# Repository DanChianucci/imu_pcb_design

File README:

This Board is an Arduino Compatable IMU/MARGS solution.
Given the Correct Firmware this unit can calculate its orientation 
relative to the earth at any given time.

IMU = Inertial Measurement Unit
MARGS = Magnetic, Angular Rate, Gravity Sensor

Main Parts include:

ITG3200 	    3 axis gyroscope
ADXL345 	    3 axis accelerometer
HMC5883L 	    3 axis magnetometer
ATMEGA328P 	    Microcontroller
ATMEGA8U2 	    USB Microcontroller
PCA9306DCUR 	i2c logic level translator

!!!!!!!!NOTE!!!!!!!!!!!
	-I recently recieved the pcb and assembled my first unit.  It works perfectly.
	 However, the Resonator that I ordered (in the parts list) is too big to fit on the footprint.
	 Instead use a CSTCE16 from Murata.
	 
	 The 3x4 Interupt/ IO select header will not work with standard male headers because the holes are too small.
	 Workaround by using swiss machine pin headers, or headers with a small diameter pin.

These Schematics and Board Layout Files were created using EagleCad Which can be
found at:
    http://www.cadsoftusa.com/
	
Additionally, many footprints and symbols were taken from the Sparkfun Eagle 
Library which can be found at:
	https://github.com/sparkfun/SparkFun-Eagle-Library

This project is not affiliated with Arduino which can be read about at:
	http://www.arduino.cc/

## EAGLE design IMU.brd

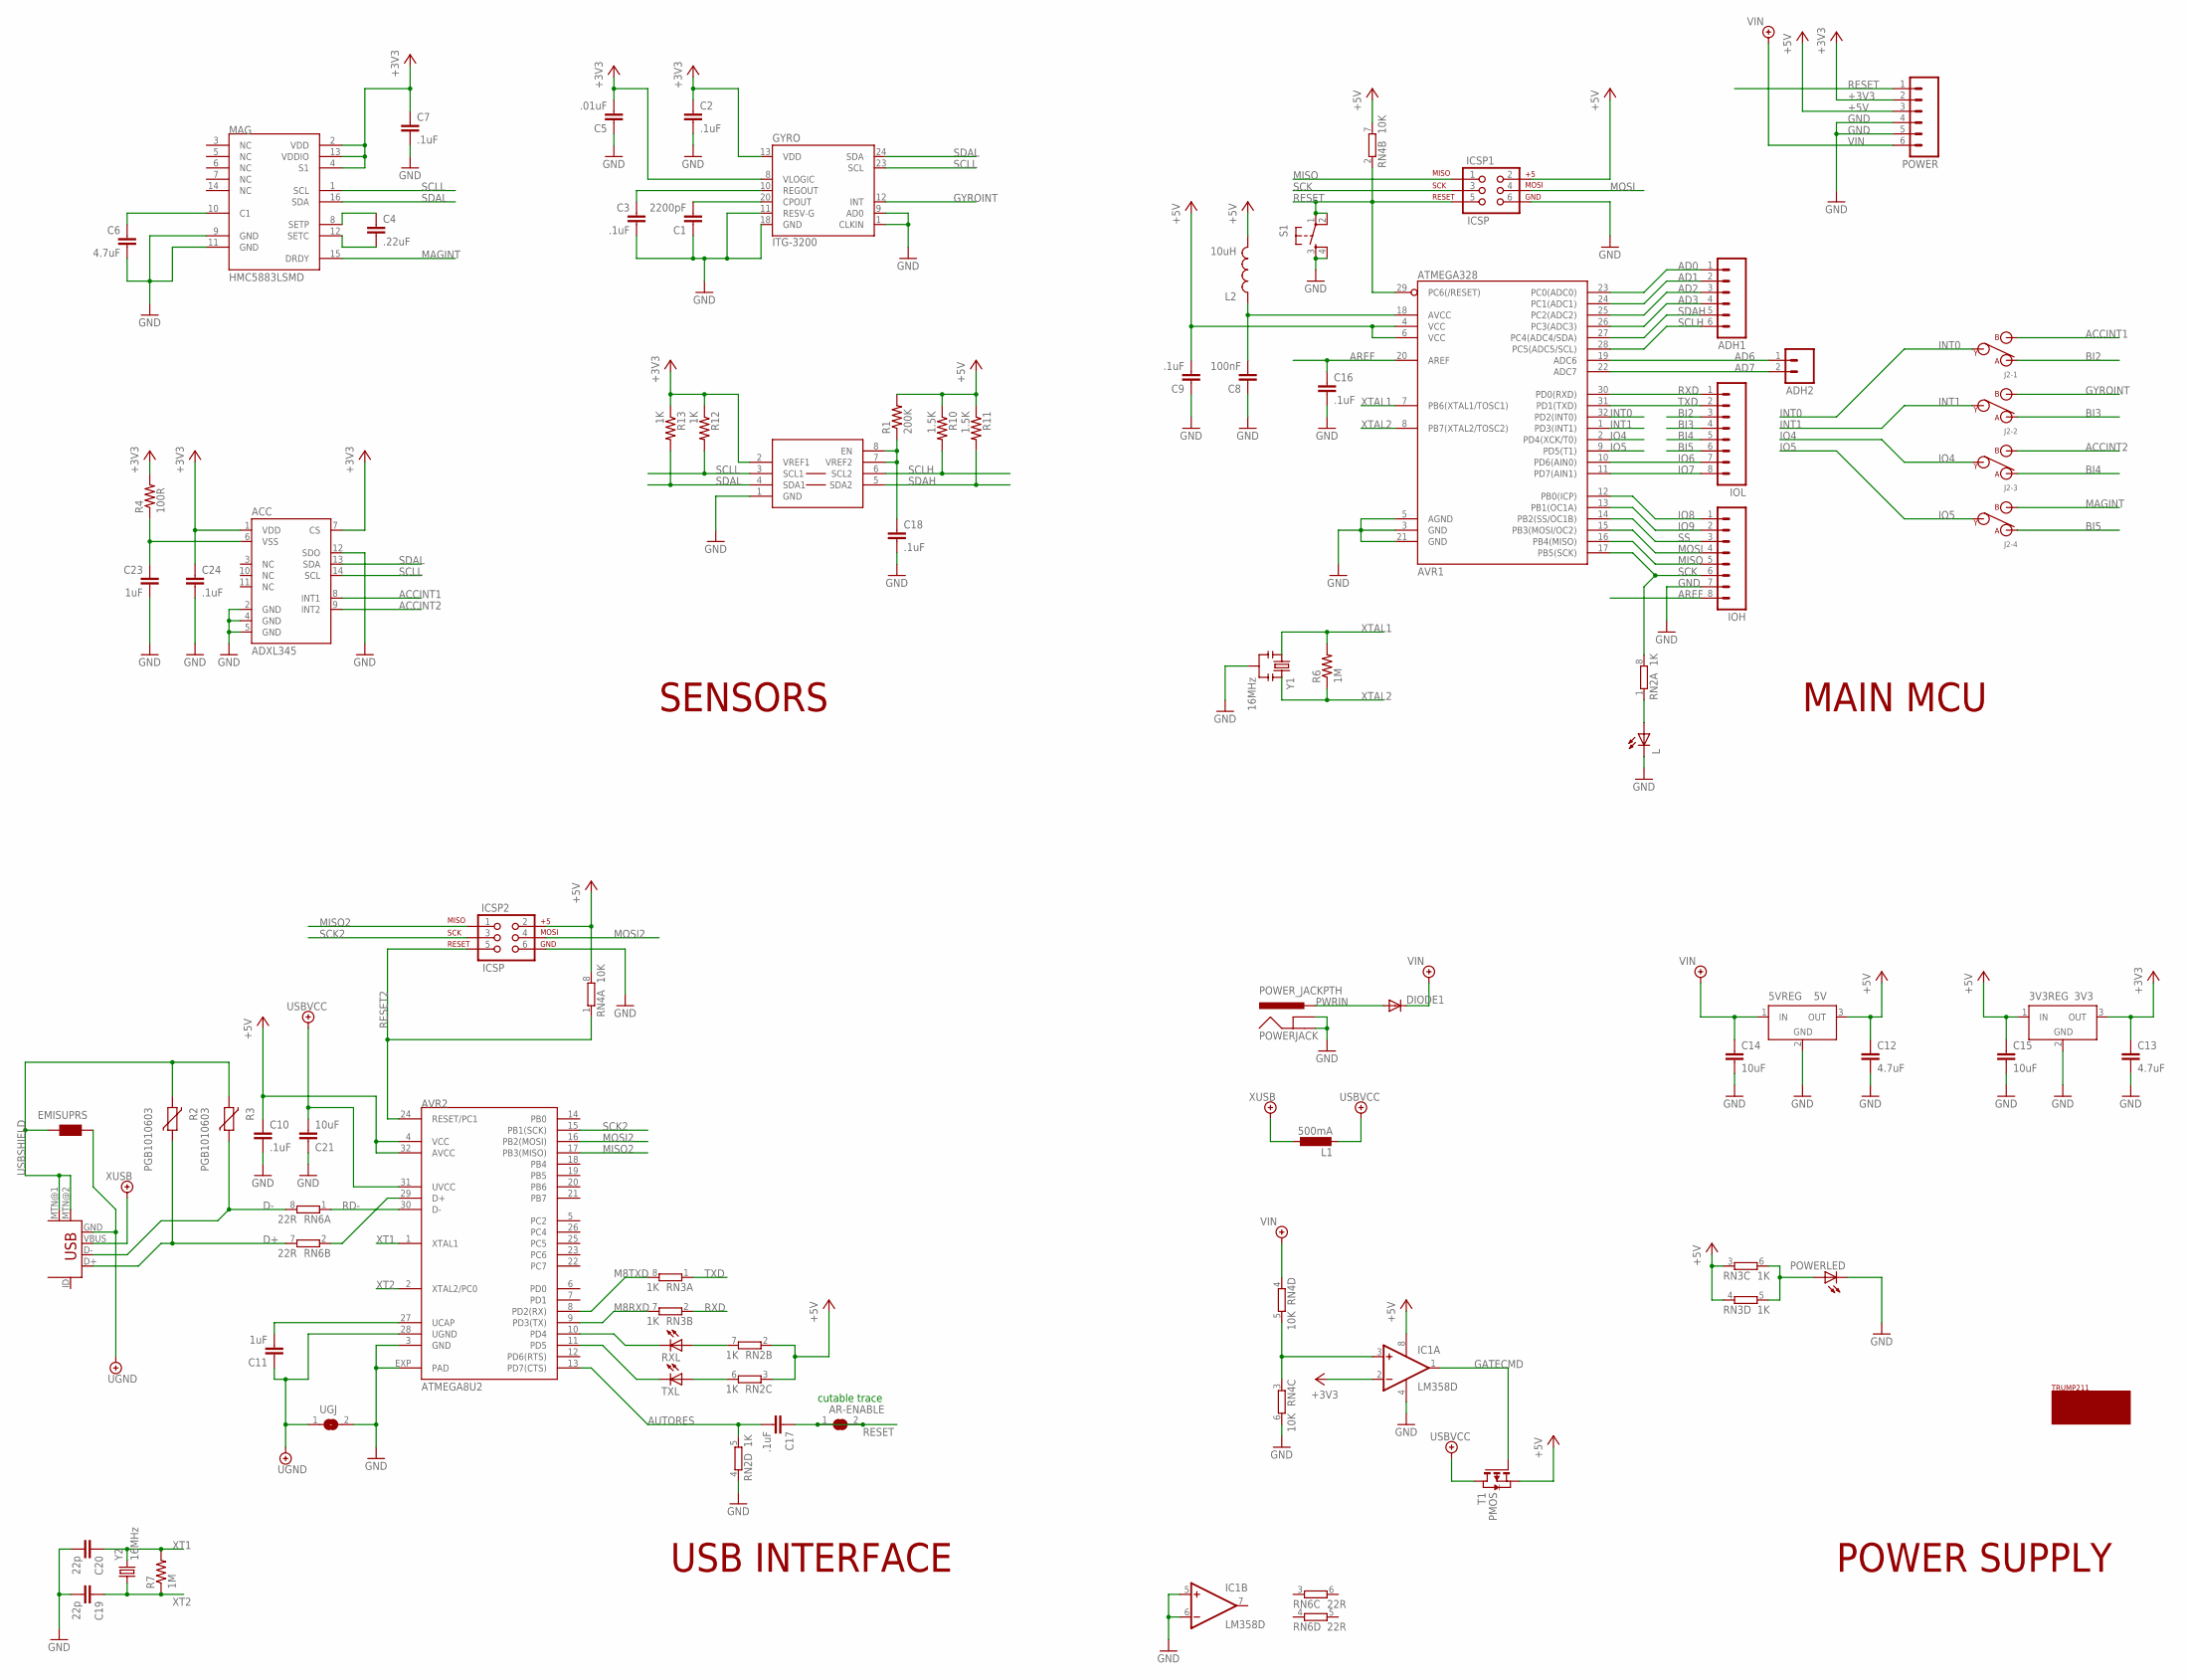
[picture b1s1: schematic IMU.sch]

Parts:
3V3REG: 3V3; SOT223
5VREG: 5V; SOT223
ACC: ADXL345; LGA14
ADH1: M06LOCK; 1X06_LOCK
ADH2: M02LOCK; 1X02_LOCK
AR-ENABLE: SJ
AVR1: ATMEGA328; TQFP32-08
AVR2: ATMEGA8U2; QFN32
C1: 2200pF; C0603
C2, C3, C7, C9, C10, C16, C17, C18, C24: .1uF; C0603
C4: .22uF; C0805
C5: .01uF; C0603
C6: 4.7uF; C0805
C8: 100nF; C0603
C11: 1uF; C0603
C12, C13: 4.7uF; C1206
C14, C15: 10uF; C1206
C19, C20: 22p; C0603
C21: 10uF; C0805
C23: 1uF; C0805
DIODE1: DIODESMA; SMA-DIODE
EMISUPRS: WE-CBF_0805; 0805
GYRO: ITG-3200; QFN-24
IC1: LM358D; SO08
ICSP1, ICSP2: ICSP; 2X3_LOCK
IOH: M08LOCK; 1X08_LOCK
IOL: M08LOCK; 1X08_LOCK
J2: 4POS_SPDT_DIP; 4X3_JUMP
L: LEDCHIP-LED0805; CHIP-LED0805
L1: 500mA; L1812
L2: 10uH; 0805
MAG: HMC5883LSMD; 16LPCC
MINIUSB: USBMINI
POWER: M06LOCK; 1X06_LOCK
POWERJACK: POWER_JACKPTH; POWER_JACK_PTH
POWERLED: LEDCHIP-LED0805; CHIP-LED0805
R1: 200K; R0603
R2, R3: PGB1010603; CT/CN0603
R4: 100R; R0603
R6, R7: 1M; R0603
R10, R11: 1.5K; R0603
R12, R13: 1K; R0603
RN2, RN3: 1K; CAY16
RN4: 10K; CAY16
RN6: 22R; CAY16
RXL: LEDCHIP-LED0805; CHIP-LED0805
S1: TAC_SWITCHSMD; TACTILE_SWITCH_SMD
T1: PMOS; SOT-23
TRANSLATOR: PCA9306; PSOP-8
TXL: LEDCHIP-LED0805; CHIP-LED0805
U$1: TRUMPLOGO
UGJ: SJ
Y1: 16MHz; RESONATOR-SMD
Y2: 16MHz; CRYSTALSMD

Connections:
5VREF: C18.1, R1.1, TRANSLATOR.7 (VREF2), TRANSLATOR.8 (EN)
+3V3: 3V3REG.3 (OUT), ACC.1 (VDD), ACC.7 (CS), C2.1, C5.2, C7.1, C13.1, C24.1, GYRO.8 (VLOGIC), GYRO.13 (VDD), IC1.2 (-IN), MAG.2 (VDD), MAG.4 (S1), MAG.13 (VDDIO), POWER.2, R4.2, R12.1, R13.1, TRANSLATOR.2 (VREF1)
+5V: 3V3REG.1 (IN), 5VREG.3 (OUT), AVR1.4 (VCC), AVR1.6 (VCC), AVR2.4 (VCC), AVR2.32 (AVCC), C9.2, C10.1, C12.1, C15.1, IC1.8 (V+), ICSP1.2, ICSP2.2, L2.2, POWER.3, R1.2, R10.1, R11.1, RN2.2 (1), RN2.3 (1), RN3.3 (1), RN3.4 (1), RN4.7 (2), RN4.8 (2), T1.2 (S)
ACCINT1: ACC.8 (INT1), J2.R1 (B)
ACCINT2: ACC.9 (INT2), J2.R3 (B)
AD0: ADH1.1, AVR1.23 (PC0(ADC0))
AD1: ADH1.2, AVR1.24 (PC1(ADC1))
AD2: ADH1.3, AVR1.25 (PC2(ADC2))
AD3: ADH1.4, AVR1.26 (PC3(ADC3))
AD6: ADH2.1, AVR1.19 (ADC6)
AD7: ADH2.2, AVR1.22 (ADC7)
AREF: AVR1.20 (AREF), C16.1, IOH.8
AUTORES: AVR2.13 (PD7(CTS)), C17.2, RN2.5 (2)
BI2: IOL.3, J2.L1 (A)
BI3: IOL.4, J2.L2 (A)
BI4: IOL.5, J2.L3 (A)
BI5: IOL.6, J2.L4 (A)
CPOUT: C1.2, GYRO.20 (CPOUT)
D+: MINIUSB.D+, R2.1, RN6.7 (2)
D-: MINIUSB.D-, R3.1, RN6.8 (2)
GATECMD: IC1.1 (OUT), T1.3 (G)
GND: 3V3REG.2 (GND), 3V3REG.4 (GND), 5VREG.2 (GND), 5VREG.4 (GND), ACC.2 (GND), ACC.4 (GND), ACC.5 (GND), ACC.12 (SDO), AVR1.3 (GND), AVR1.5 (AGND), AVR1.21 (GND), AVR2.3 (GND), AVR2.EXP (PAD), C1.1, C2.2, C3.2, C5.1, C6.2, C7.2, C8.1, C9.1, C10.2, C12.2, C13.2, C14.2, C15.2, C16.2, C18.2, C19.2, C20.2, C21.1, C23.2, C24.2, GYRO.1 (CLKIN), GYRO.9 (AD0), GYRO.11 (RESV-G), GYRO.18 (GND), IC1.4 (V-), IC1.5 (+IN), IC1.6 (-IN), ICSP1.6, ICSP2.6, IOH.7, L.C, MAG.9 (GND), MAG.11 (GND), POWER.4, POWER.5, POWERJACK.GND, POWERJACK.GNDBREAK, POWERLED.C, RN2.4 (1), RN4.6 (2), S1.3, S1.4, TRANSLATOR.1 (GND), UGJ.2, Y1.2, Y2.2 (GND), Y2.4 (GND)
GYROINT: GYRO.12 (INT), J2.R2 (B)
INT0: AVR1.32 (PD2(INT0)), J2.M1 (Y)
INT1: AVR1.1 (PD3(INT1)), J2.M2 (Y)
IO4: AVR1.2 (PD4(XCK/T0)), J2.M3 (Y)
IO5: AVR1.9 (PD5(T1)), J2.M4 (Y)
IO6: AVR1.10 (PD6(AIN0)), IOL.7
IO7: AVR1.11 (PD7(AIN1)), IOL.8
IO8: AVR1.12 (PB0(ICP)), IOH.1
IO9: AVR1.13 (PB1(OC1A)), IOH.2
M8RXD: AVR2.9 (PD3(TX)), RN3.7 (2)
M8TXD: AVR2.8 (PD2(RX)), RN3.8 (2)
MAGINT: J2.R4 (B), MAG.15 (DRDY)
MISO: AVR1.16 (PB4(MISO)), ICSP1.1, IOH.5
MISO2: AVR2.17 (PB3(MISO)), ICSP2.1
MOSI: AVR1.15 (PB3(MOSI/OC2)), ICSP1.4, IOH.4
MOSI2: AVR2.16 (PB2(MOSI)), ICSP2.4
unnamed: C6.1, MAG.10 (C1)
unnamed: C3.1, GYRO.10 (REGOUT)
unnamed: ACC.6 (VSS), C23.1, R4.1
unnamed: RN2.7 (2), RXL.A
unnamed: RN2.6 (2), TXL.A
unnamed: AVR1.18 (AVCC), C8.2, L2.1
unnamed: L.A, RN2.1
PWRIN: DIODE1.A, POWERJACK.PWR
PWRLED: POWERLED.A, RN3.5 (2), RN3.6 (2)
RD+: AVR2.29 (D+), RN6.2 (1)
RD-: AVR2.30 (D-), RN6.1
RESET: AR-ENABLE.1, AR-ENABLE.2, AVR1.29 (PC6(/RESET)), C17.1, ICSP1.5, POWER.1, RN4.2 (1), S1.1, S1.2
RESET2: AVR2.24 (RESET/PC1), ICSP2.5, RN4.1
RXD: AVR1.30 (PD0(RXD)), IOL.1, RN3.2 (1)
RXLED: AVR2.10 (PD4), RXL.C
SCK: AVR1.17 (PB5(SCK)), ICSP1.3, IOH.6, RN2.8 (2)
SCK2: AVR2.15 (PB1(SCK)), ICSP2.3
SCLH: ADH1.6, AVR1.28 (PC5(ADC5/SCL)), R10.2, TRANSLATOR.6 (SCL2)
SCLL: ACC.14 (SCL), GYRO.23 (SCL), MAG.1 (SCL), R12.2, TRANSLATOR.3 (SCL1)
SDAH: ADH1.5, AVR1.27 (PC4(ADC4/SDA)), R11.2, TRANSLATOR.5 (SDA2)
SDAL: ACC.13 (SDA), GYRO.24 (SDA), MAG.16 (SDA), R13.2, TRANSLATOR.4 (SDA1)
SETC: C4.2, MAG.12 (SETC)
SETP: C4.1, MAG.8 (SETP)
SS: AVR1.14 (PB2(SS/OC1B)), IOH.3
TXD: AVR1.31 (PD1(TXD)), IOL.2, RN3.1
TXLED: AVR2.11 (PD5), TXL.C
UGND: AVR2.28 (UGND), C11.1, EMISUPRS.1, MINIUSB.GND, UGJ.1
USBSHIELD: EMISUPRS.2, MINIUSB.MTN@1, MINIUSB.MTN@2, R2.2, R3.2
USBVCC: AVR2.31 (UVCC), C21.2, L1.2, T1.1 (D)
VIN: 5VREG.1 (IN), C14.1, DIODE1.C, POWER.6, RN4.4 (1)
VIN/2: IC1.3 (+IN), RN4.3 (1), RN4.5 (2)
VUCAP: AVR2.27 (UCAP), C11.2
XT1: AVR2.1 (XTAL1), C20.1, R7.2, Y2.3 (2)
XT2: AVR2.2 (XTAL2/PC0), C19.1, R7.1, Y2.1
XTAL1: AVR1.7 (PB6(XTAL1/TOSC1)), R6.2, Y1.1
XTAL2: AVR1.8 (PB7(XTAL2/TOSC2)), R6.1, Y1.3
XUSB: L1.1, MINIUSB.VBUS

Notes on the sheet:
POWER SUPPLY
USB INTERFACE
MAIN MCU
SENSORS
cutable trace

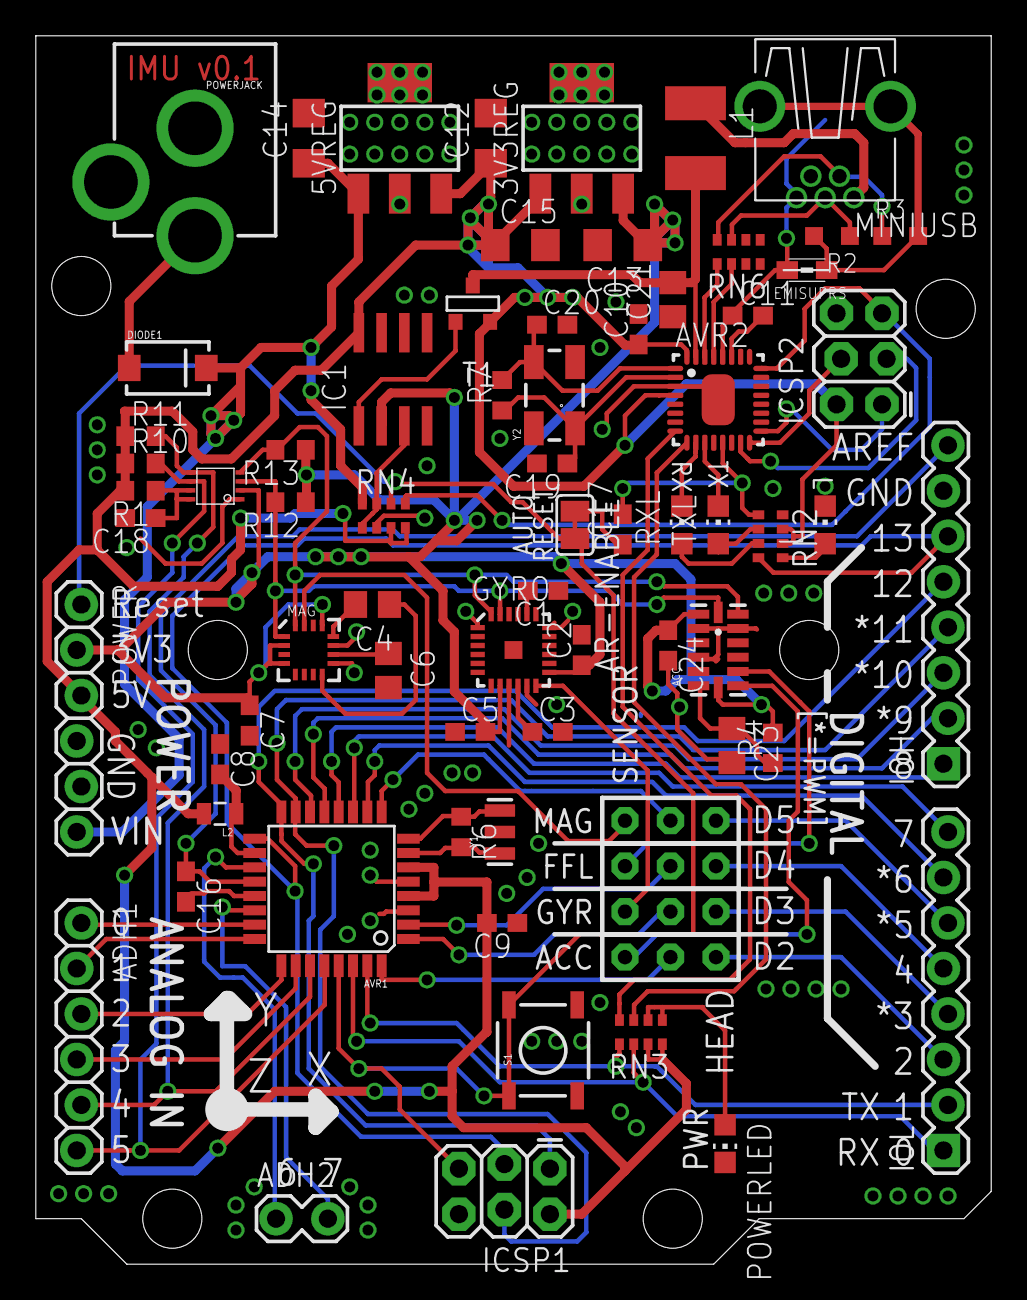
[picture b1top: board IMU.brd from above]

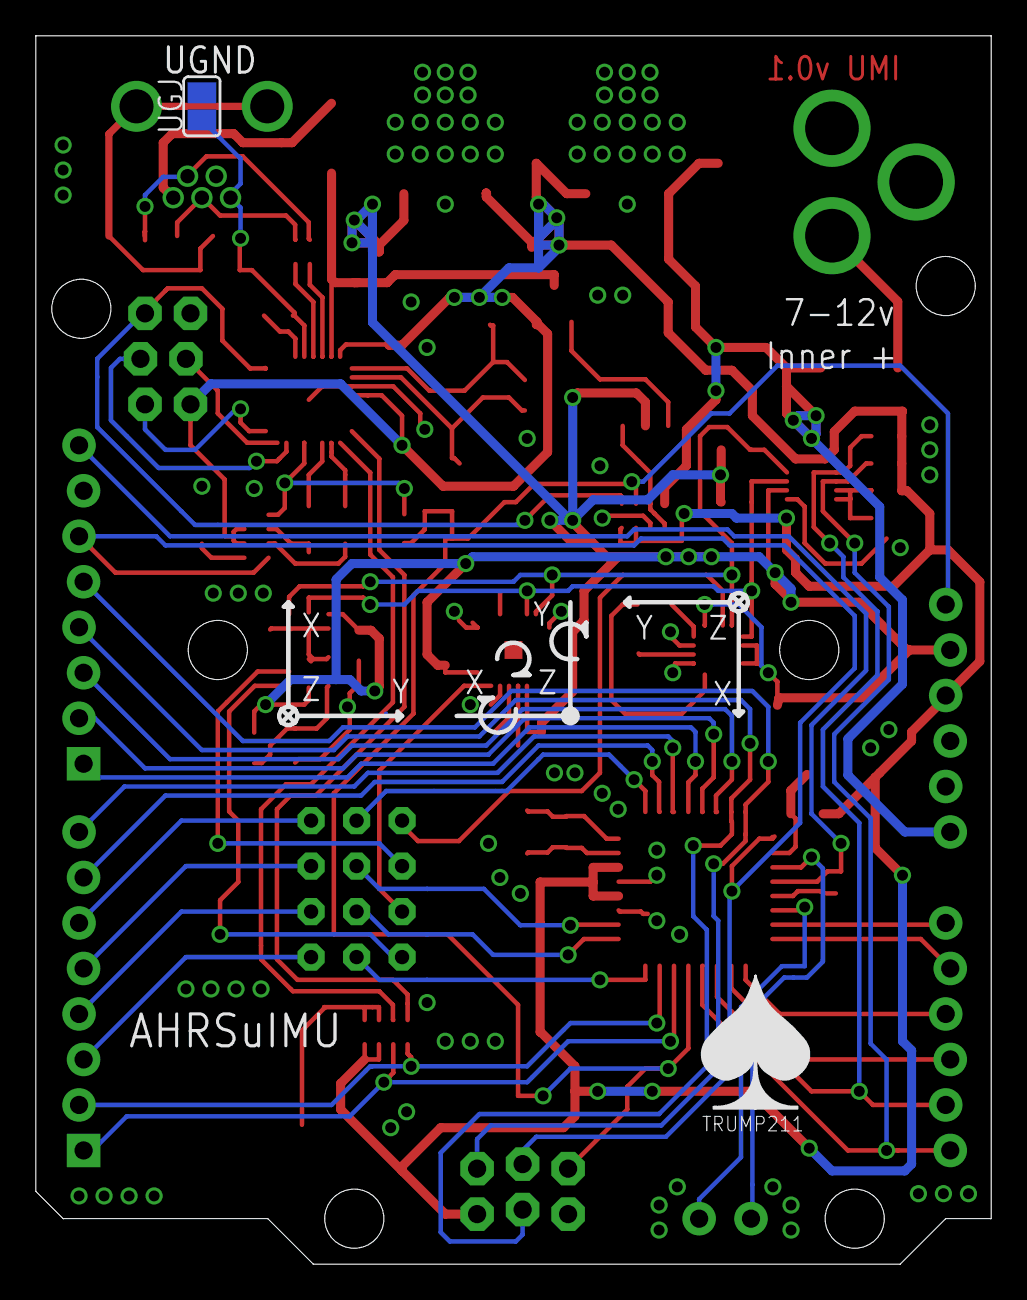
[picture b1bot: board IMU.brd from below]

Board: 2 copper layers, 53.3 x 68.6 mm, 80 parts (2 on the bottom side), 75 nets.

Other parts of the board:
JP1, JP2, JP3, JP4, JP5, JP9: STAND-OFF
U$17: TRI_AXIS_DECAL_GYRO; THREE_AXISGYRO_DECAL
U$18, U$19: TRI_AXIS_DECAL; THREEAXIS

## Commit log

2011-05-16 Testing
2011-05-16 deleted pong.jar
2011-05-16 Added Initial Imu Board not really sure what all these files are
2011-05-16 Added Revision two, including the elimination of all old files
2011-06-19 Schematic on single sheet
2011-06-19 Removed Uneeded Files b# and s# files
2011-06-19 Updated Schematic
2011-07-01 Added jumpers to select between bidirectional sensor lines, or sensor interupts
2011-07-02 Began Power Distribution Calculations... resistors values still need to be checked and finalized.
2011-07-02 Began a bill of materials including prices and distributors
2011-07-02 Added imu.xls, with some miscelaneous information
2011-07-05 Cleaned up and Added silkscreen labels to brd file.
2011-07-07 Touched Up silkscreen labels. Added labels to the solder jumpers (RESET EN and UGND), and LED's.
2011-07-07 more labels on board file
2011-07-07 fixed broken equations. everything should work correctly, still need to enter some data
2011-07-26 Test commit from new computer
2011-07-27 Test commit from SmartGit
2011-07-28 Determined Resistor power usage. Green = I'm pretty sure they aren't using power that isn't accounted for in the IC datasheets. Grey = not sure.
2011-07-28 Fixed missing airwire
2011-07-30 Added a real Readme
2011-08-05 Low side i2c pullups now 1k (used to be 983R)
2011-08-05 Better resistor descriptions, all resistors now accounted for. Regulator Power calculations might be a little messed up
2011-08-05 updated BOM to include the actual circuit board
2011-08-07 Full Bom includes every part needed to make the board, plus distributors where i found the best price
2011-08-07 Updated power distribution with correct gnd currents, and finalised the part number of the regulator i will be using
2011-08-07 changed capacitor C6 to 0805 from 0603 package in order to make it easier to obtain. Changed layout accordingly
2011-08-07 [BOM] decided to use an 0603 .1uF cap as the filter on the translator. The datasheet did't have a recomended value.
2011-08-08 Added 7bit binary addresses to the i2c address list
2011-08-08 added imu checklist.xls went through data sheets and listed all external parts needed for each ic
2011-08-08 Corrected Resonator is now 16MHz (was 10)
2011-08-08 Moved some vias to make room for bottom side silk screen. tidied up various traces
2011-08-08 added .1uF bypass cap to hmc5883
2011-08-08 Checked all externally needed parts.
2011-08-08 input cap on the voltage regulators changed for a part with higher voltage rating.
2011-08-08 Added mine.lbr, which contains some additional footprints used on the board (mainly just the atmega8u2)
2011-08-09 added 100ohm capacitor in series with the adxl345 as per the datasheet
2011-08-09 rechecked datasheets again, (found some errors highlighted in red, semi errors in yellow)
2011-08-09 Transitioned to the tantalum caps where needed (BOM,Checklist, and PCB)
2011-08-09 added 10uF cap on usbvcc, don't need low pass on atmega8u2 because not using analog capabilities.
2011-08-09 Need 10uF cap on usbvccc, dont need lowpass on atmega8u2 because not using analog capabilities
2011-08-09 added low pass filter to atmega328p, added 10uF cap to usbvcc, various rerouting
2011-08-10 Added decals showing the axis to the silkscreen
2011-08-12 Low Filteron 328p, and Cap on usbvcc are added
2011-08-12 tripled up the vias on 5v line, previously all current would flow through single via when powered by usb
2011-08-13 Made the footprints of the two caps on the hmc5883L 0805, just to make it easier to find parts that meet the esr spec.
2011-08-13 Found part numbers for transistor, usbvcc cap, and added another ,1uF cap for the low pass filter
2011-08-13 Changed size of transistor to 0805 to find part more easily
2011-08-14 Everything accounted for except the hmc5883l caps need to be checked for low esr
2011-08-14 All parts added, including newly added parts, and finally got around to finding suitable leds
2011-08-24 Fixed som SKU for newark which linked to minimum orders in the thousands. Switch some parts to Newark as distributor to make it easier to order
2011-11-07 Moved to new EagleCad beta xml file format
2011-11-23 Switched back to Eagle 5 binary format due to problems with the Eagle 6 beta interface. Redid the Schematic To make it easier to read
2011-11-23 Updated BOM with correct ordered quant and cost
2012-06-16 BRD cleanup, Moved to new Eagle 6 Format again, Reference Designators Updated in XLS files
2012-07-09 Updated Readme to reflect current project status
2012-07-16 Updated BOM to reflect change in Resonator Cleaned Up Directory
2022-12-09 Made some fixes for missing libraries

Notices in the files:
parts and their libraries:
SparkFun-Passives: Licensing: CC v3.0 Share-Alike You are welcome to use this library for commercial purposes.
